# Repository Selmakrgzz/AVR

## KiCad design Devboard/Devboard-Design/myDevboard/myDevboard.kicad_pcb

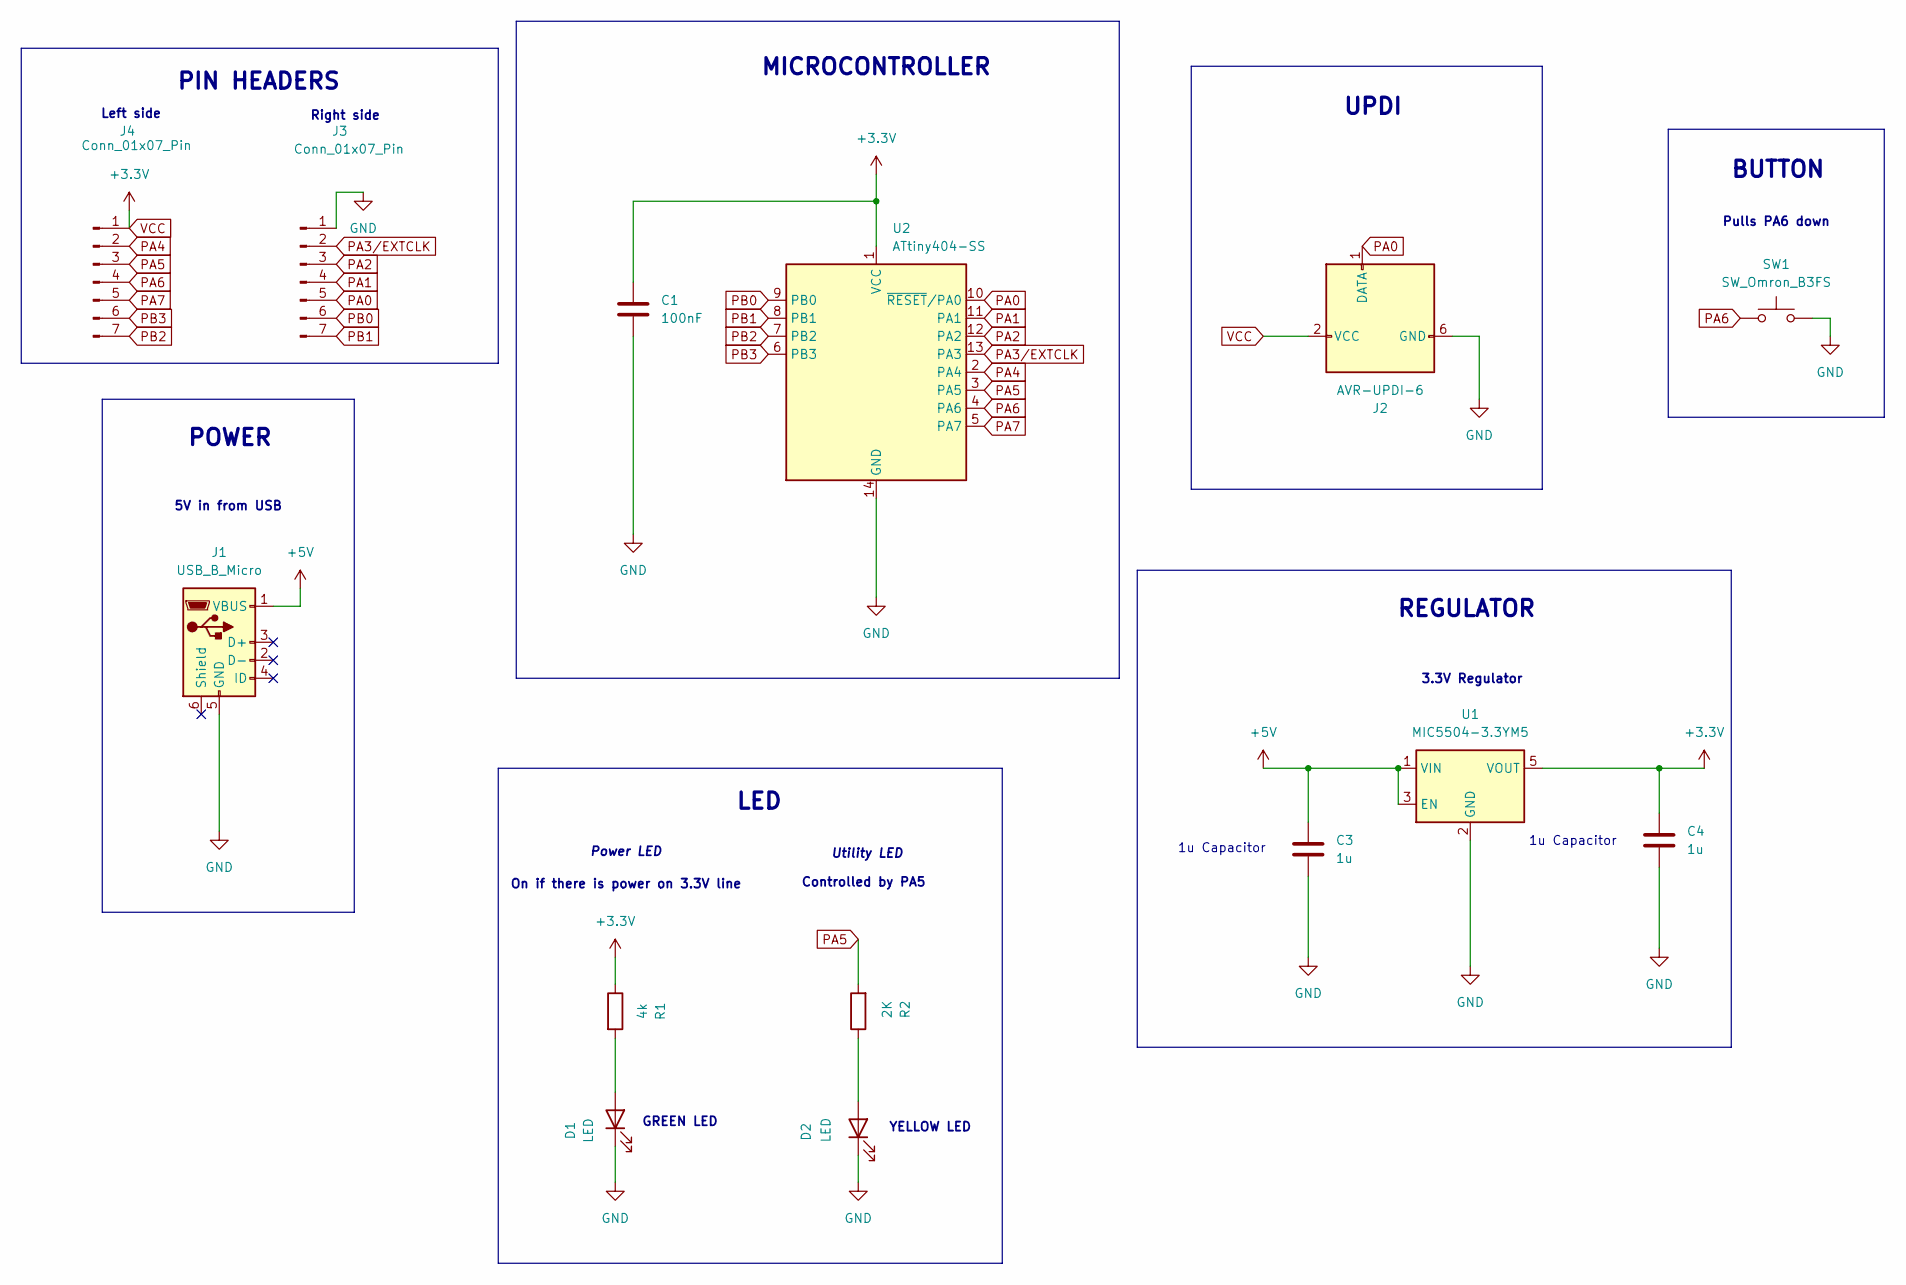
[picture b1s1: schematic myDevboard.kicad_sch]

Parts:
C1: 100nF; C_0603_1608Metric
C3, C4: 1u; C_0603_1608Metric
D1, D2: LED; LED_0603_1608Metric
J1: USB_B_Micro; USB_Micro-B_Amphenol_10104110_Horizontal
J2: AVR-UPDI-6; PinHeader_2x03_P2.54mm_Vertical
J3, J4: Conn_01x07_Pin; PinHeader_1x07_P2.54mm_Vertical
R1: 4k; R_0603_1608Metric
R2: 2K; R_0603_1608Metric
SW1: SW_Omron_B3FS; SW_TH_Tactile_Omron_B3F-10xx
U1: MIC5504-3.3YM5; SOT-23-5
U2: ATtiny404-SS; SOIC-14_3.9x8.7mm_P1.27mm

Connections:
+5V: C3.1, J1.1 (VBUS), U1.1 (VIN), U1.3 (EN)
GND: C1.2, C3.2, C4.2, D1.1 (K), D2.1 (K), J1.5 (GND), J2.6 (GND), J3.1, SW1.2, U1.2 (GND), U2.14 (GND)
unnamed: D1.2 (A), R1.2
unnamed: D2.2 (A), R2.1
PA0: J2.1 (DATA), J3.5, U2.10 (~RESET/PA0)
PA1: J3.4, U2.11 (PA1)
PA2: J3.3, U2.12 (PA2)
PA3/EXTCLK: J3.2, U2.13 (PA3)
PA4: J4.2, U2.2 (PA4)
PA5: J4.3, R2.2, U2.3 (PA5)
PA6: J4.4, SW1.1, U2.4 (PA6)
PA7: J4.5, U2.5 (PA7)
PB0: J3.6, U2.9 (PB0)
PB1: J3.7, U2.8 (PB1)
PB2: J4.7, U2.7 (PB2)
PB3: J4.6, U2.6 (PB3)
VCC: C1.1, C4.1, J2.2 (VCC), J4.1, R1.1, U1.5 (VOUT), U2.1 (VCC)

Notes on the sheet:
GREEN LED
PIN HEADERS
REGULATOR
3.3V Regulator
Power LED
5V in from USB
1u Capacitor
BUTTON
On if there is power on 3.3V line
YELLOW LED
Right side
POWER
MICROCONTROLLER
Utility LED
UPDI
Left side
Controlled by PA5
LED
Pulls PA6 down

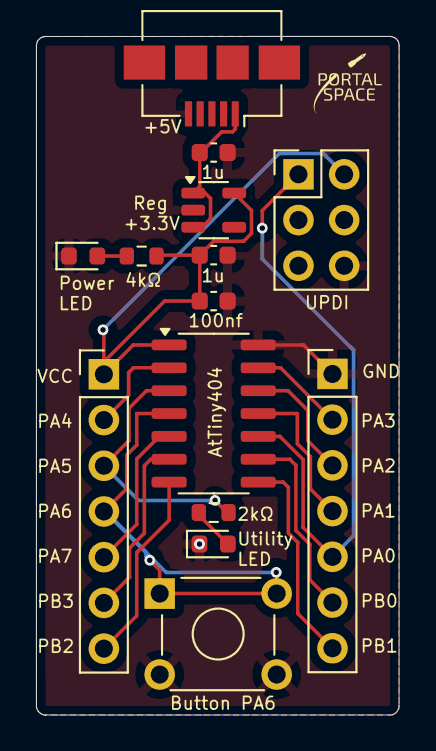
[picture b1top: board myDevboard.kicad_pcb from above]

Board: 2 copper layers, 20.1 x 37.7 mm, 14 parts (0 on the bottom side), 17 nets.

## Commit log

2024-11-02 The code runs
2025-01-12 Add devboard design folder
2025-02-02 Add new lab project - digital communication
2025-02-02 Reorganize the folder structure
2025-02-02 Delete .vs/commLab/v14 directory
    I dunno
